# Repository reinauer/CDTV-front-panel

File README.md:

# Commodore AMIGA CDTV front panel

This is a reproduction of the CDTV front panel.

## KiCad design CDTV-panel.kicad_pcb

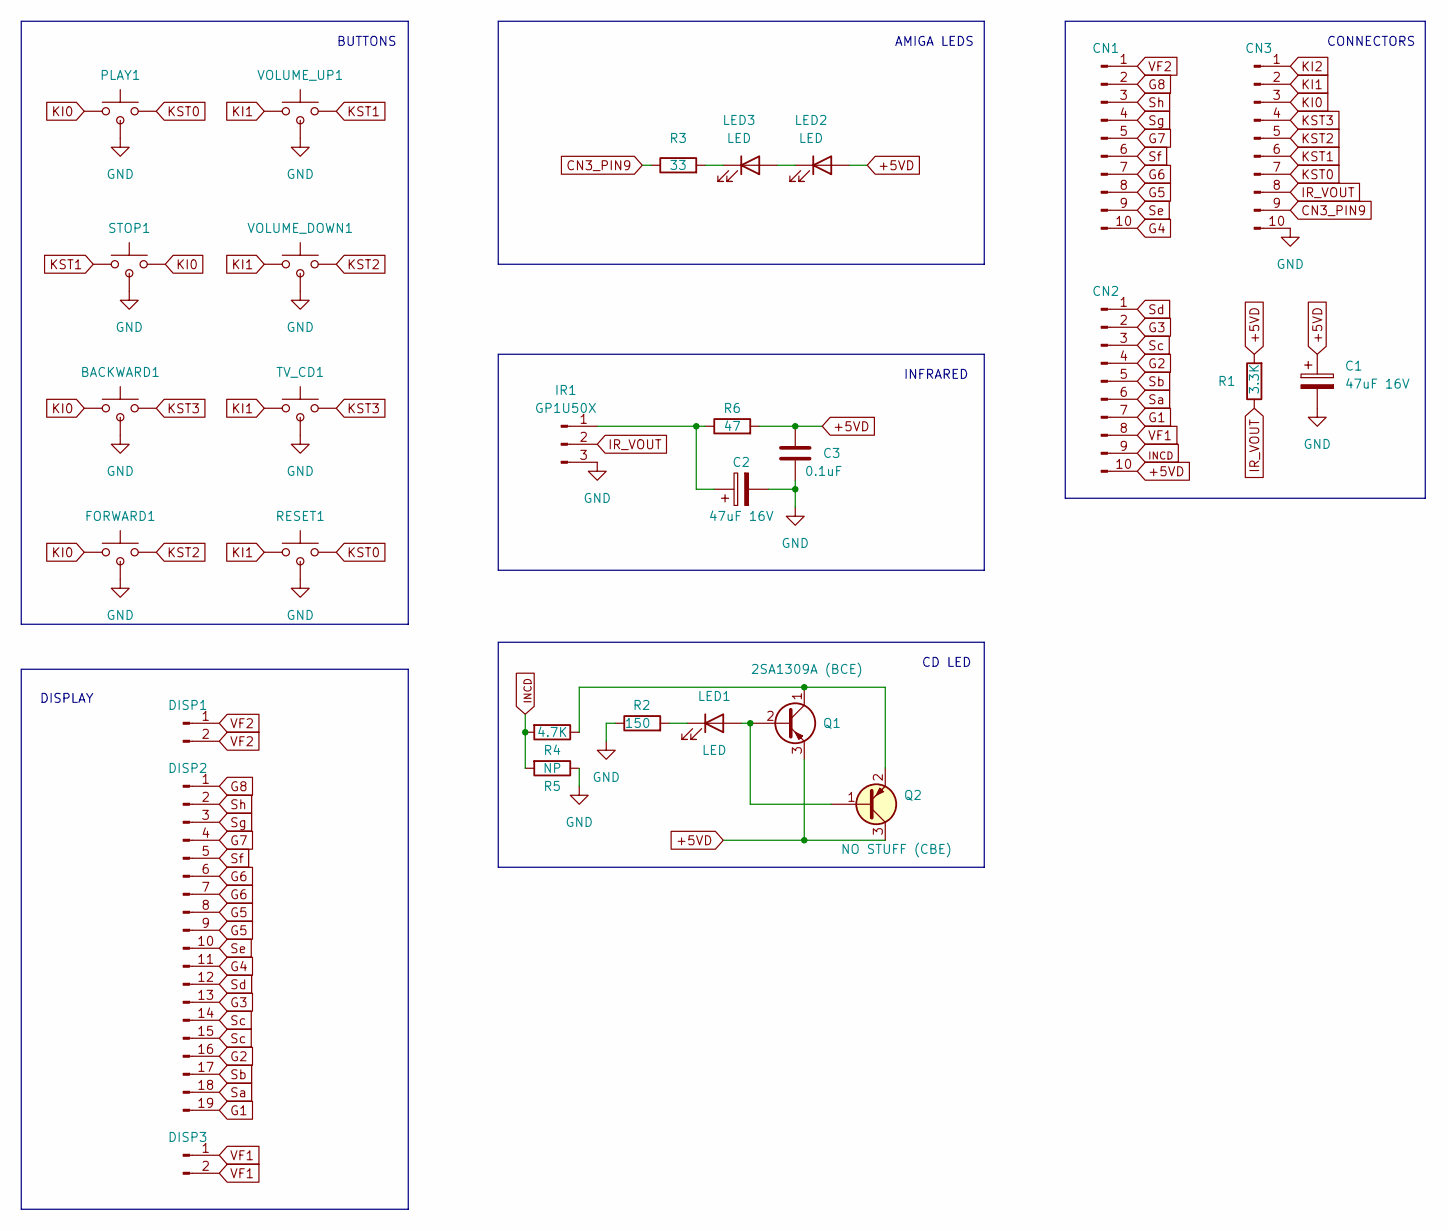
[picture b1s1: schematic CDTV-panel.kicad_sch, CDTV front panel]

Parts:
BACKWARD1: SW_Push_CDTV; PushButton_6x6mm_TH
C1, C2: 47uF 16V; CP_Radial_D6.3mm_P3.8mm
C3: 0.1uF; Cap_Ceramic_TH
CN1, CN2, CN3: PinSocket_1x10_P2.00mm_Vertical
DISP1: PinSocket_1x19_P2.54mm_Vertical; Pin_Header_Straight_1x02
DISP2: Pin_Header_Straight_1x02; PinSocket_1x19_P2.54mm_Vertical
DISP3: Pin_Header_Straight_1x02
FORWARD1: SW_Push_CDTV; PushButton_6x6mm_TH
IR1: GP1U50X; OSRB8C9BA_Horizontal
LED1: LED; LED_Rectangular_W5.0mm_H2.0mm
LED2, LED3: LED; LED_D5.0mm
PLAY1: SW_Push; PushButton_6x6mm_TH
Q1: 2SA1309A (BCE); TO-220-3_Vertical_BCE
Q2: NO STUFF (CBE); TO-220-3_Vertical_CBE
R1: 3.3K; R_Axial_DIN0207_L6.3mm_D2.5mm_P10.16mm_Horizontal
R2: 150; R_Axial_DIN0207_L6.3mm_D2.5mm_P10.16mm_Horizontal
R3: 33; R_Axial_DIN0207_L6.3mm_D2.5mm_P10.16mm_Horizontal
R4: 4.7K; R_Axial_DIN0207_L6.3mm_D2.5mm_P10.16mm_Horizontal
R5: NP; R_Axial_DIN0207_L6.3mm_D2.5mm_P10.16mm_Horizontal
R6: 47; R_Axial_DIN0207_L6.3mm_D2.5mm_P10.16mm_Horizontal
RESET1: SW_Push_CDTV; PushButton_6x6mm_TH
STOP1: SW_Push_CDTV; PushButton_6x6mm_TH
TV_CD1: SW_Push_CDTV; PushButton_6x6mm_TH
VOLUME_DOWN1: SW_Push_CDTV; PushButton_6x6mm_TH
VOLUME_UP1: SW_Push_CDTV; PushButton_6x6mm_TH

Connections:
+5VD: C1.1, C3.1, CN2.10, LED2.2 (A), Q1.3 (E), Q2.3 (E), R1.2, R6.2
CN3_PIN9: CN3.9, R3.1
G1: CN2.7, DISP2.19
G2: CN2.4, DISP2.16
G3: CN2.2, DISP2.13
G4: CN1.10, DISP2.11
G5: CN1.8, DISP2.8, DISP2.9
G6: CN1.7, DISP2.6, DISP2.7
G7: CN1.5, DISP2.4
G8: CN1.2, DISP2.1
GND: BACKWARD1.3 (GND), C1.2, C2.2, C3.2, CN3.10, FORWARD1.3 (GND), IR1.3, IR1.4, IR1.5, PLAY1.3 (GND), R2.1, R5.1, RESET1.3 (GND), STOP1.3 (GND), TV_CD1.3 (GND), VOLUME_DOWN1.3 (GND), VOLUME_UP1.3 (GND)
IR_VOUT: CN3.8, IR1.2, R1.1
KI0: BACKWARD1.1, CN3.3, FORWARD1.1, PLAY1.1, STOP1.2
KI1: CN3.2, RESET1.1, TV_CD1.1, VOLUME_DOWN1.1, VOLUME_UP1.1
KI2: CN3.1
KST0: CN3.7, PLAY1.2, RESET1.2
KST1: CN3.6, STOP1.1, VOLUME_UP1.2
KST2: CN3.5, FORWARD1.2, VOLUME_DOWN1.2
KST3: BACKWARD1.2, CN3.4, TV_CD1.2
unnamed: C2.1, IR1.1, R6.1
unnamed: LED1.2 (A), Q1.2 (B), Q2.1 (C)
unnamed: LED1.1 (K), R2.2
unnamed: LED2.1 (K), LED3.2 (A)
unnamed: LED3.1 (K), R3.2
unnamed: Q1.1 (C), Q2.2 (B), R4.1
Sa: CN2.6, DISP2.18
Sb: CN2.5, DISP2.17
Sc: CN2.3, DISP2.14, DISP2.15
Sd: CN2.1, DISP2.12
Se: CN1.9, DISP2.10
Sf: CN1.6, DISP2.5
Sg: CN1.4, DISP2.3
Sh: CN1.3, DISP2.2
VF1: CN2.8, DISP3.1, DISP3.2
VF2: CN1.1, DISP1.1, DISP1.2
_{INCD}: CN2.9, R4.2, R5.2

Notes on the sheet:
AMIGA LEDS
CD LED
DISPLAY
CONNECTORS
BUTTONS
INFRARED

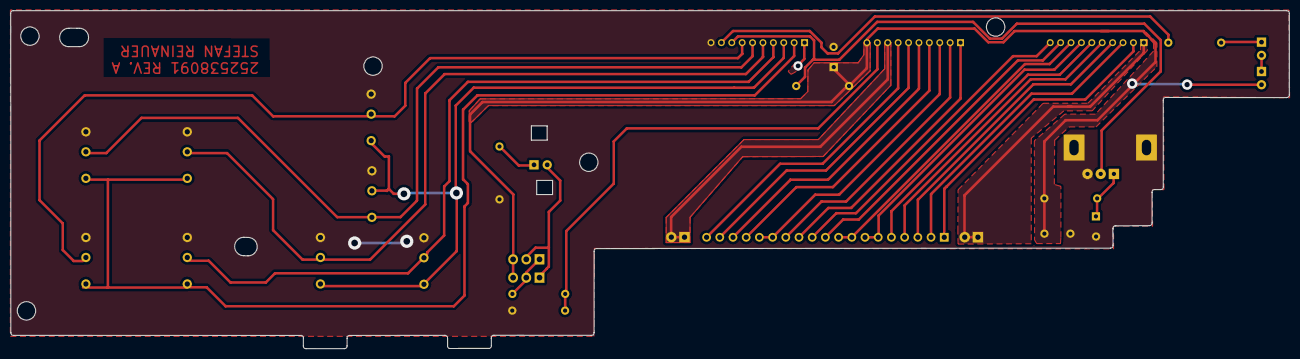
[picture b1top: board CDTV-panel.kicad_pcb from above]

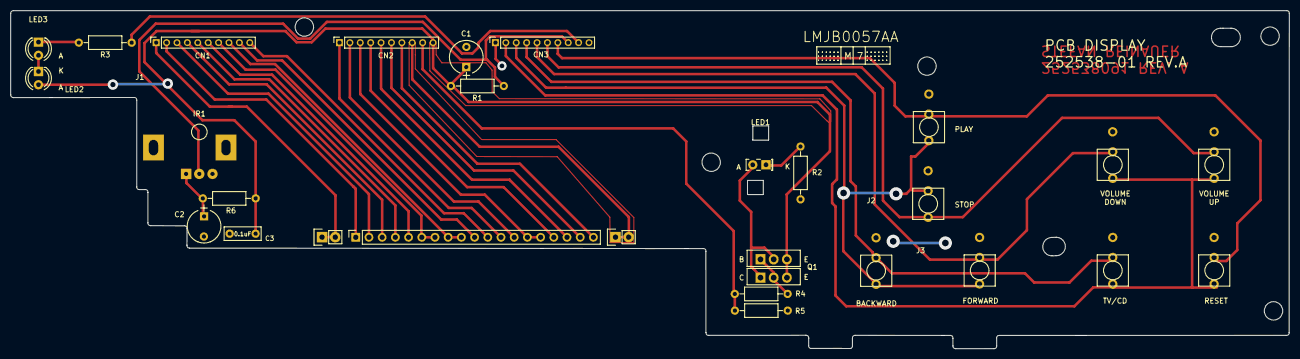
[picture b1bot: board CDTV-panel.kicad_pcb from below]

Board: 2 copper layers, 245.9 x 65.0 mm, 29 parts (29 on the bottom side), 35 nets.

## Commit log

2024-02-18 Add picture of PCB
2024-02-18 Add sym-lib-table
2024-02-19 Update graphcis

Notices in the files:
CDTV-panel.kicad_sch:
© 2024-02  Stefan Reinauer
